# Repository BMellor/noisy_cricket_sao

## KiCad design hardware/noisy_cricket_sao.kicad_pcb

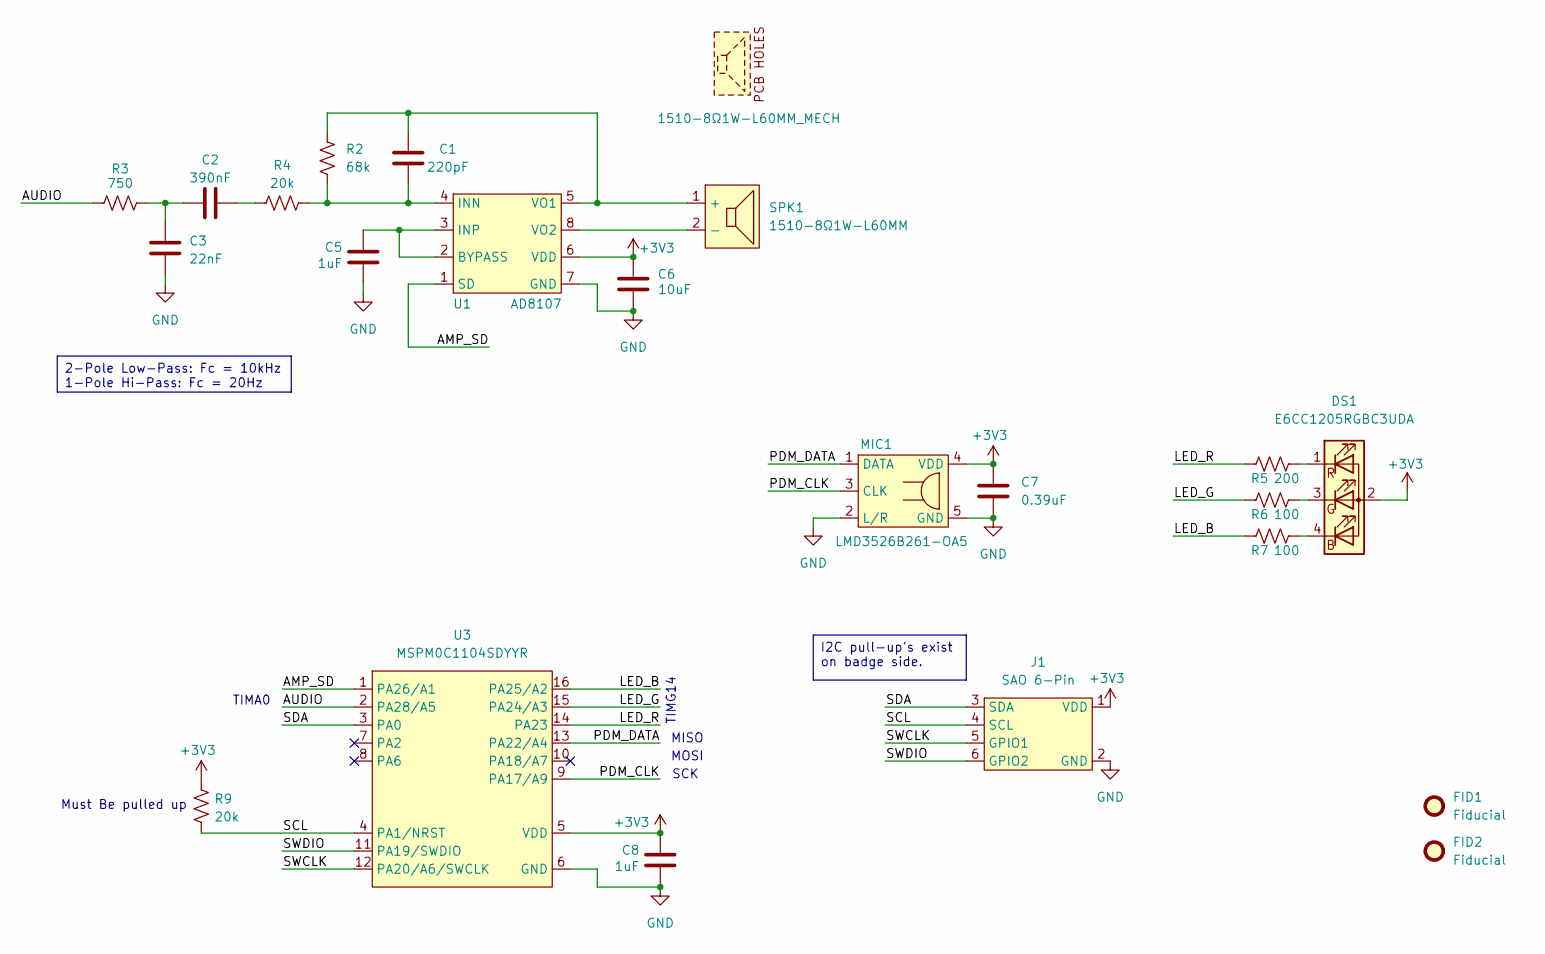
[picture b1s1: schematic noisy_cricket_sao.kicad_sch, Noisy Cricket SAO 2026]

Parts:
C1: 220pF; C_0402_1005Metric
C2: 390nF; C_0402_1005Metric
C3: 22nF; C_0402_1005Metric
C5, C8: 1uF; C_0402_1005Metric
C6: 10uF; C_0603_1608Metric
C7: 0.39uF; C_0402_1005Metric
DS1: E6CC1205RGBC3UDA
FID1, FID2: Fiducial; Fiducial_0.5mm_Mask1.5mm
J1: SAO 6-Pin; PinHeader_2x03_P2.54mm_Vertical_SMD
MECH1: 1510-8Ω1W-L60MM_MECH
MIC1: LMD3526B261-OA5
R2: 68k; R_0402_1005Metric
R3: 750; R_0402_1005Metric
R4, R9: 20k; R_0402_1005Metric
R5: 200; R_0402_1005Metric
R6, R7: 100; R_0402_1005Metric
SPK1: 1510-8Ω1W-L60MM; 1510-8Ω1W-L60MM_SMT_PADS
U1: AD8107
U3: MSPM0C1104SDYYR; SOT23-16-TI

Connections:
+3V3: C6.1, C7.2, C8.2, DS1.2 (A), J1.1 (VDD), MIC1.4 (VDD), R9.1, U1.6 (VDD), U3.5 (VDD)
/AMP_SD: U1.1 (SD), U3.1 (PA26/A1)
/AUDIO: R3.1, U3.2 (PA28/A5)
/LED_B: R7.1, U3.16 (PA25/A2)
/LED_G: R6.1, U3.15 (PA24/A3)
/LED_R: R5.1, U3.14 (PA23)
/PDM_CLK: MIC1.3 (CLK), U3.9 (PA17/A9)
/PDM_DATA: MIC1.1 (DATA), U3.13 (PA22/A4)
/SCL: J1.4 (SCL), R9.2, U3.4 (PA1/NRST)
/SDA: J1.3 (SDA), U3.3 (PA0)
/SWCLK: J1.5 (GPIO1), U3.12 (PA20/A6/SWCLK)
/SWDIO: J1.6 (GPIO2), U3.11 (PA19/SWDIO)
GND: C3.2, C5.1, C6.2, C7.1, C8.1, J1.2 (GND), MIC1.2 (L/R), MIC1.5 (GND), U1.7 (GND), U1.9 (EP), U3.6 (GND)
unnamed: C2.1, C3.1, R3.2
unnamed: C2.2, R4.1
unnamed: DS1.4 (BK), R7.2
unnamed: DS1.3 (GK), R6.2
unnamed: DS1.1 (RK), R5.2
unnamed: C1.1, R2.2, SPK1.1 (+), U1.5 (VO1)
unnamed: SPK1.2 (-), U1.8 (VO2)
unnamed: C5.2, U1.2 (BYPASS), U1.3 (INP)
unnamed: C1.2, R2.1, R4.2, U1.4 (INN)

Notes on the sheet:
TIMG14
MISO
Must Be pulled up
TIMA0
SCK
MOSI
2-Pole Low-Pass: Fc = 10kHz 1-Pole Hi-Pass: Fc = 20Hz
I2C pull-up's exist on badge side.

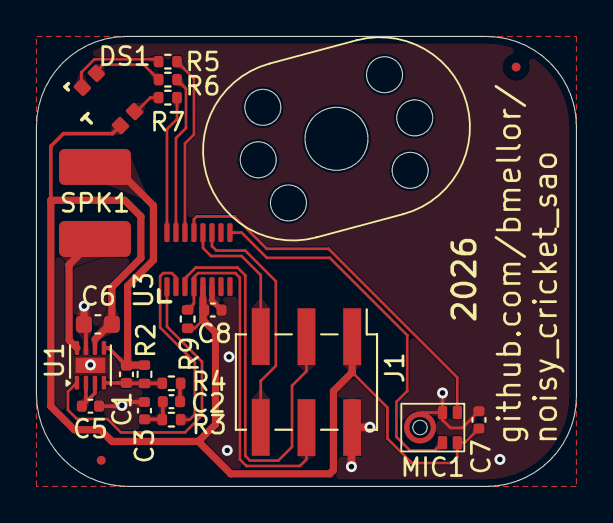
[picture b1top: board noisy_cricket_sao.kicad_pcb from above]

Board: 2 copper layers, 30.0 x 25.0 mm, 23 parts (0 on the bottom side), 22 nets.

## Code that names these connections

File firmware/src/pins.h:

#pragma once

#include <stdint.h>
#include <ti/devices/msp/msp.h>
#include <ti/devices/msp/peripherals/hw_gpio.h>

typedef struct {
  GPIO_Regs *port;
  const uint32_t pinmask;
  const uint32_t iomux;
} gpio_pin_t;

static const gpio_pin_t SDA = {GPIOA, (1 << 0), IOMUX_PINCM1};        // PA0  (I2C0_SDA[3])
static const gpio_pin_t SCL_NRST = {GPIOA, (1 << 1), IOMUX_PINCM2};   // PA1  (I2C0_SCL[2] / NRST)
static const gpio_pin_t PDM_CLK = {GPIOA, (1 << 17), IOMUX_PINCM18};  // PA17 (SPI0_SCK[4])
static const gpio_pin_t SWDIO = {GPIOA, (1 << 19), IOMUX_PINCM20};    // PA19
static const gpio_pin_t SWCLK = {GPIOA, (1 << 20), IOMUX_PINCM21};    // PA20
static const gpio_pin_t PDM_DATA = {GPIOA, (1 << 22), IOMUX_PINCM23}; // PA22 (SPI0_POCI[3] i.e. MISO)
static const gpio_pin_t LED_R = {GPIOA, (1 << 23), IOMUX_PINCM24};    // PA23 (TIMG14_C0[4])
static const gpio_pin_t LED_G = {GPIOA, (1 << 24), IOMUX_PINCM25};    // PA24 (TIMG14_C1[3])
static const gpio_pin_t LED_B = {GPIOA, (1 << 25), IOMUX_PINCM26};    // PA25 (TIMG14_C3[2])
static const gpio_pin_t AMP_SD = {GPIOA, (1 << 26), IOMUX_PINCM27};   // PA26
static const gpio_pin_t AUDIO = {GPIOA, (1 << 28), IOMUX_PINCM29};    // PA28 (TIMA0_C0[2])

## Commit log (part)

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2026-02-14 Submodule ch32fun, setup empty KiCAD project, update .gitignore
2026-02-15 Create part symbols, working on schematic.
2026-02-15 Add datasheets
2026-02-16 Finish schematic
2026-02-16 Create empty footprints, add low pass filter to amp
2026-02-21 Add footprints and models, start part positioning.
2026-04-28 Initial ugly routing of PCB
2026-04-28 2nd ugly route complete
2026-04-29 cleaned up routing
2026-04-30 Add panelization and fab files.
2026-04-30 add windowpane to microphone ground ring
2026-05-23 move/fix ch32fun submodule
2026-05-23 Get template project building in VSCode. Improve build process later.
